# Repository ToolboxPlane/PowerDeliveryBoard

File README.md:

View this project on [CADLAB.io](https://cadlab.io/node/755). 

# PowerDeliveryBoard

This board provides and monitors a 5V and 3.3V rail and monitors battery voltage and current.

Top Side|Bottom Side
:-------------------------:|:-------------------------:
|

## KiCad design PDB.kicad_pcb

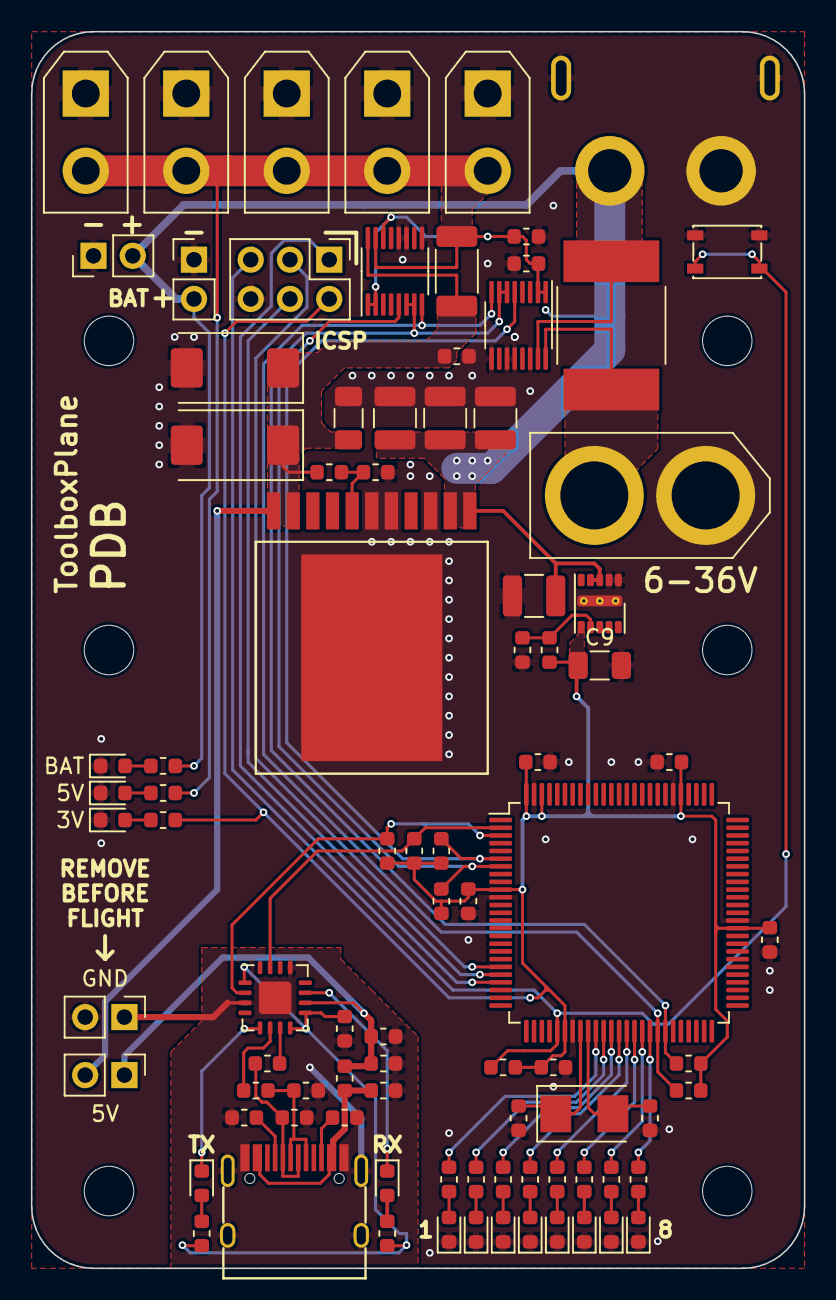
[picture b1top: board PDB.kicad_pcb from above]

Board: 2 copper layers, 50.0 x 80.0 mm, 95 parts (0 on the bottom side), 53 nets.

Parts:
C1, C2: 8pF; C_0603_1608Metric
C3, C4, C5, C6, C7, C14, C16: 100nF; C_0603_1608Metric
C8: 10µF; C_1210_3225Metric
C9: 22µF; C_1206_3216Metric
C10, C24: 100n; C_0603_1608Metric
C11, C12: 47p; C_0603_1608Metric
C13: 10nF; C_0603_1608Metric
C15: 4.7µF; C_0603_1608Metric
C17, C18, C19: 10µ; C_1210_3225Metric
C20: 47n; C_0603_1608Metric
C21, C22: 330µ; CP_EIA-7343-31_Kemet-D
C23: 47µ; C_1206_3216Metric
D1: blue; LED_0603_1608Metric
D2: green; LED_0603_1608Metric
D3: orange; LED_0603_1608Metric
D4, D5, D6, D7, D8, D9, D10, D11: LED_0603_1608Metric
D12, D13: LED_Small; LED_0603_1608Metric
FB1: 600 Ohms @ 100MHz; C_0603_1608Metric
H1, H2, H3, H4, H5, H6: MountingHole; MountingHole_3.2mm_M3
J1, J2, J3, J4, J5: Conn_01x02; AMASS_XT30UPB-F_1x02_P5.0mm_Vertical
J6, J7: Conn_01x02; PinHeader_1x02_P2.54mm_Vertical
J8: Conn_01x02; XT60PB-M
J9: Conn_02x03_Odd_Even; PinHeader_2x03_P2.54mm_Vertical
J10: Conn_01x02_MountingPin; XT60PW-F
J11: USB_C_Receptacle_USB2.0; USB_C_Receptacle_GT-USB-7010
JP1, JP2: Jumper; PinHeader_1x02_P2.54mm_Vertical
R1, R29: 2.8k; R_0603_1608Metric
R2, R3, R14, R15, R16, R17, R18: 10k; R_0603_1608Metric
R4: 470; R_0603_1608Metric
R5, R26, R27: 270; R_0603_1608Metric
R6, R7, R8, R9, R10, R11, R12, R13: 100; R_0603_1608Metric
R19: 11.5k; R_0603_1608Metric
R20: 4.99k; R_0603_1608Metric
R21: 2m; R_3920
R22, R23: 5.1k; R_0603_1608Metric
R24, R25: 27; R_0603_1608Metric
R28: 14.7k; R_0603_1608Metric
R30: 8m; R_2010_5025Metric
SW1: SW_Push; SW_SPST_PTS810
U1: ATmega2560-16AU; TQFP-100_14x14mm_P0.5mm
U2: LMZM23600; Texas_SIL0010A_MicroSiP-10-1EP_3.8x3mm_P0.6mm_EP0.7x2.9mm_T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
U3, U6: LTC2946; MSOP-16_3x4mm_P0.5mm
U4: FT230XQ; QFN-16-1EP_4x4mm_P0.65mm_EP2.1x2.1mm
U5: LMZ13608
Y1: 16MHz; Crystal_SMD_5032-2Pin_5.0x3.2mm

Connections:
+3V3: C3.2, C4.2, C5.2, C6.2, C7.2, C9.1, J9.2, R2.1, R3.1, R5.1, R14.1, R15.1, R16.1, R17.1, R18.1, R19.1, U1.10, U1.31, U1.61, U1.80, U1.98, U1.100, U2.6
+5V: C10.1, C24.1, J1.2, J2.2, J3.2, J4.2, J5.2, R4.1, R30.1, U3.1, U3.2, U6.1, U6.2, U6.14, U6.15
+BATT: C8.1, C17.1, C18.1, C19.1, J6.2, J7.2, J10.2, R1.1, R21.1, U2.3, U2.4, U3.15, U5.1, U5.2
/5V/5VIN: C20.1, C21.1, C22.1, C23.1, JP1.2, R28.1, R30.2, U5.10, U5.11, U6.16
/ATMega/MISO: J9.1, U1.22
/ATMega/MOSI: J9.4, U1.21
/ATMega/SCK: J9.3, U1.20
/ATMega/~RESET~: J9.5, R14.2, SW1.2, U1.30
/BAT/VBATIN: J8.2, R21.2, U3.16
/FT230/5VOUT: C14.1, C15.1, FB1.1, JP1.1, U4.10
/RX: R2.2, U1.2, U4.15
/SCL: R16.2, U1.43, U3.8, U6.8
/SDA: R15.2, U1.44, U3.6, U3.7, U6.6, U6.7
/TX: R3.2, U1.3, U4.2
/~ALERT_+5V~: R18.2, U1.7, U6.5
/~ALERT_VBAT~: R17.2, U1.6, U3.5
GND: C1.2, C2.2, C3.1, C4.1, C5.1, C6.1, C7.1, C8.2, C9.2, C10.2, C17.2, C18.2, C19.2, C20.2, C21.2, C22.2, C23.2, C24.2, D1.1, D2.1, D3.1, D4.1, D5.1, D6.1, D7.1, D8.1, D9.1, D10.1, D11.1, J1.1, J2.1, J3.1, J4.1, J5.1, J6.1, J7.1, J8.1, J9.6, J10.1, J10.MP, JP2.2, R20.1, R29.2, SW1.1, U1.11, U1.32, U1.62, U1.81, U1.99, U2.1, U2.2, U2.11, U3.9, U3.11, U3.12, U3.14, U5.3, U5.5, U5.6, U5.PAD, U6.9, U6.11, U6.12
GNDS: C11.2, C12.2, C13.2, C14.2, C15.2, C16.2, J11.A1, J11.A12, J11.B1, J11.B12, J11.S1, JP2.1, R22.1, R23.1, U4.3, U4.13, U4.17
unnamed: C1.1, U1.34, Y1.2
unnamed: C2.1, U1.33, Y1.1
unnamed: C11.1, J11.A7, J11.B7, R24.2
unnamed: C12.1, J11.A6, J11.B6, R25.2
unnamed: C16.1, R26.1, R27.1, U4.1, U4.8, U4.9
unnamed: D1.2, R1.2
unnamed: D2.2, R4.2
unnamed: D3.2, R5.2
unnamed: D4.2, R6.2
unnamed: D5.2, R7.2
unnamed: D6.2, R8.2
unnamed: D7.2, R9.2
unnamed: D8.2, R10.2
unnamed: D9.2, R11.2
unnamed: D10.2, R12.2
unnamed: D11.2, R13.2
unnamed: D12.1, U4.11
unnamed: D12.2, R26.2
unnamed: D13.1, U4.5
unnamed: D13.2, R27.2
unnamed: J11.A5, R22.2
unnamed: J11.B5, R23.2
unnamed: R6.1, U1.35
unnamed: R7.1, U1.36
unnamed: R8.1, U1.37
unnamed: R9.1, U1.38
unnamed: R10.1, U1.39
unnamed: R11.1, U1.40
unnamed: R12.1, U1.41
unnamed: R13.1, U1.42
unnamed: R19.2, R20.2, U2.7
unnamed: R24.1, U4.7
unnamed: R25.1, U4.6
unnamed: R28.2, R29.1, U5.7
VBUS: C13.1, FB1.2, J11.A4, J11.A9, J11.B4, J11.B9

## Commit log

2018-01-03 added gitignore
2018-01-04 Connected Levelshifter
2018-01-04 First parts placed
2018-01-04 added temperature sensor
2018-01-04 updated inductor for 3v regulator
2018-01-04 added mounting holes
2018-01-08 AT30TS74 connected
2018-01-09 Header connected, First Layout attempt
2018-01-09 5v nearly completely connected
2018-01-11 First Layout GND not connected because of wrong design rules
2018-01-12 fixed spi level shifting
2018-01-15 First Version, nearly completed
2018-01-22 added net classes
2018-01-22 assigned net classes
2018-01-22 fixed some signal trace widths
2018-01-23 ISP, SPI, I2C Bus layout
2018-01-23 added shunts
2018-01-24 fixed xt60, updated libs
2018-01-24 more wip
2018-01-26 changed R6
2018-01-30 fixed shunt resistor libraries
2018-01-30 fixed #5
2018-01-30 fixed vbat routing for better ground path
2018-01-30 fixed shunt resistor value
2018-01-30 design rules
2018-02-01 fixed min drill
2018-02-09 various improvements/fixes
    added power output pins
    fixed design rules
    moved ESC out to bottom
    fixed packages
    removed unnecessary filtering for atmega
    etc
2018-02-09 fixed #10
    removed expansion port connections
    rotated expansion port
    connected expansion port
    added 3V3 jumper
2018-02-09 changed atmega routing
2018-02-09 fixed via stop limit
2018-02-09 added images
2018-02-14 various changes
    removed netclasses, might add them later again, creates issues with sense lines
    fixed output pin
    version bump
    fixed some vias/drills
2018-02-14 gnd routing
    netclasses
2018-02-23 sachen gemacht dass fusion glücklich ist
2018-02-23 layout stuff
2018-02-24 multiple changes
    removed inductor,
    fixed layout + schematic
2018-03-09 Backlink to CADLAB.io has been added.
2018-03-11 various changes
    moved smd components on metric grid
    silkscreen, reduced fuckup in part sizes
    added output
2018-03-12 fixed 3d models
2018-03-12 added reset, closed #11
2018-03-12 silkscreen
2018-03-12 fixed layout, silkscreen, resistor values
2018-03-12 changed LTC2946 for easier soldering
2018-03-12 fixed atmega
    closes #12
2018-03-12 fixed naming, silkscreen
2018-03-12 silkscreen fixes
2018-03-12 added temperature alert
2018-03-12 added serial port
2018-03-12 fixed silkscreen: jp8
2018-03-12 fixed gnd routing
2018-03-12 fixed levelshifter footprint
2018-03-12 R value levelshifter
2018-03-12 ti lib update
2018-03-13 improved high current traces
2018-03-13 removed unnecessary gnd traces
2018-03-14 fixed typo
2018-03-14 Update README.md
    fixed cadlab link
2018-03-15 updated pictures in readme
2018-08-14 adds LMZ13608 lbr
2018-08-14 remove old schematic
2018-08-14 adds new empty schematic
2018-08-14 adds frame
2018-08-14 adds LMZ13608 and resistors to set output voltage
2018-08-16 Cin, formatting
2018-08-16 Cin, formatting
    not only the library file this time
2018-08-19 added ATmega2560 library
2018-08-22 added ATmega
    + crystal, ISP
2018-08-22 adds FT230X
2018-08-22 fix atmega supply voltage
    fixes #26
2018-08-22 adds LTC2946 library
2018-08-22 adds shunt_resistor lbr
2018-08-22 adds power monitoring
2018-08-22 adds 4 programmable LEDs on PL0-PL3
2018-08-30 moved *.lbr to LBR directory
2018-08-30 adds micromatch lbr
2018-08-30 adds expansion port
2018-08-30 adds lbr to gitignore
2018-09-02 3.3v regulation
2018-09-03 adds missing schottky diode for 3.3v reg
    fixes #30
2018-09-04 adds XT60
2018-09-08 adds FlightComputer USB connector
2019-01-05 kicad
2019-01-05 adds submodules
2019-02-22 assign vbat shunt footprint
2019-02-22 LMZ13608 input caps
2019-02-22 fix missing footprint
2019-02-22 LMZ13608 output caps
2019-02-22 5V shunt
2019-02-23 fix footprints
2019-02-23 fix serial connection ftdi-atmega
2019-02-23 update ottojo lib
2019-02-25 update xt60
2019-02-27 update footprints
2019-03-03 move FT230 to https://github.com/ToolboxPlane/FT230Module
2019-03-12 smaller shunt on 5v rail
2019-03-12 LMZ13608 3d model
2019-03-12 add rx/tx labels
2019-03-12 annotate parts
2019-03-12 update USB footprint
2019-03-13 add 3d model for USB-C
2019-03-13 update USB C footprint
2019-03-13 add XT30 5V Out
2019-03-13 3v3 regulator 3d model
2019-03-13 USB C Power Port
2019-03-13 layout WIP
2019-03-19 update submodule for USBC
2019-04-03 wip und so
2019-04-03 add fp-info-cache to gitignore
2019-04-03 add reset switch
2019-04-03 LMZM23600 from kicad libs
2019-04-04 remove isolation from FT230
2019-04-04 more LEDs
2019-04-04 layout
2019-04-05 more layout
2019-04-05 even more layout
2019-04-05 layout fixes, reannotate
2019-04-05 silkscreen stuff
2019-04-05 the ACTUAL silkscreen stuff, including the actual changes this time
2019-04-05 use official XT30 footprint
2019-04-05 rounded corners
2019-04-05 add missing trace near USB
2019-04-07 mounting dimensions
2019-04-07 oshw logo
2019-04-07 rebuild zones
2019-04-07 fix 3.3v regulator output cap
2019-04-07 fix thermals for 5V out
2019-04-07 layout fixes
2019-04-07 add large toolbox logo on bottom side
2019-04-27 fix LEDs
2019-04-27 fix debug LED resistors
